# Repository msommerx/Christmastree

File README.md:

# Christmastree

Advent calendar in the shape of a Christmastree.  
Based on WS2812 LEDs and an ESP8266 combined with an DS3231 RTC for non WiFi environment.  

## Hardware
I used an WEMOS D1 Mini to controll the LEDs. If you have a WiFi in range, you don't need the DS3231. Just setup the WiFi on the ESP8266 and get your time via NTP.  
In my case there was no WiFi, so I needed an extra RTC.  
The WS2812 LEDs are connected in parallel. Everything can easyly be driven by a 5V DC Powersupply. 

## Software
Based on the WS2812FX Library, beginning at the 1st of a month, the first LED turns on. The 2nd the second LED turns on and so on.  
At the 24th of a month all LEDs are turned on until the 1st of the next month.  
To hold the time, even if the circuit was disconnected, I used a battery buffered DS3231.

## Circuit Layout
The Eagle layout has only less through-plating so it can easiely be made by your own. Also the wires are sized bigger including clearence between wires and pads.

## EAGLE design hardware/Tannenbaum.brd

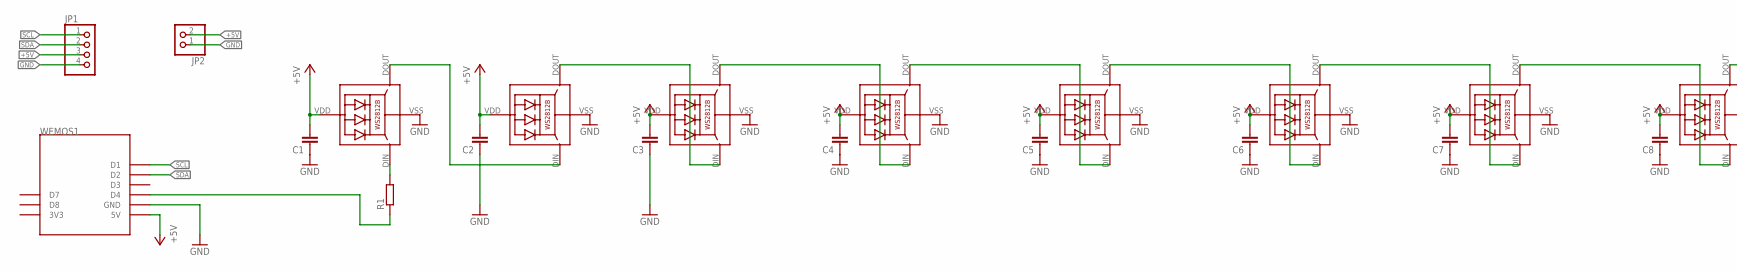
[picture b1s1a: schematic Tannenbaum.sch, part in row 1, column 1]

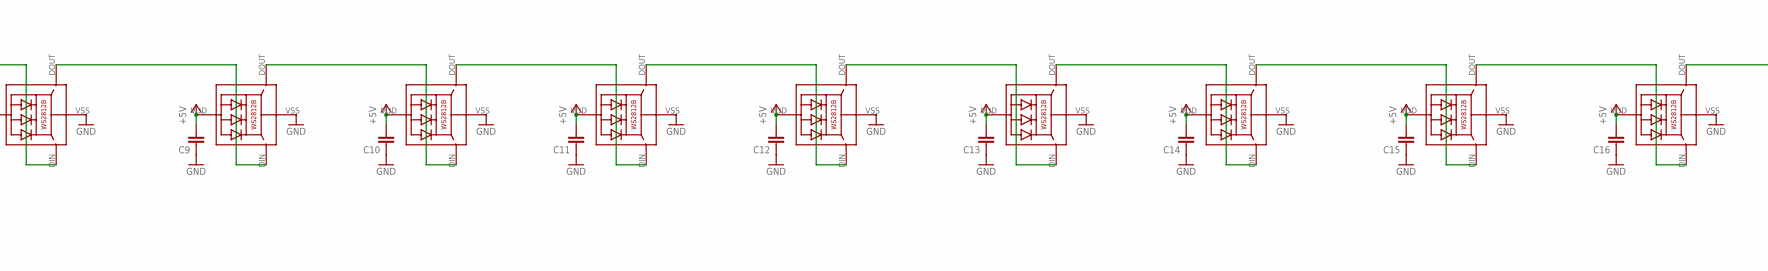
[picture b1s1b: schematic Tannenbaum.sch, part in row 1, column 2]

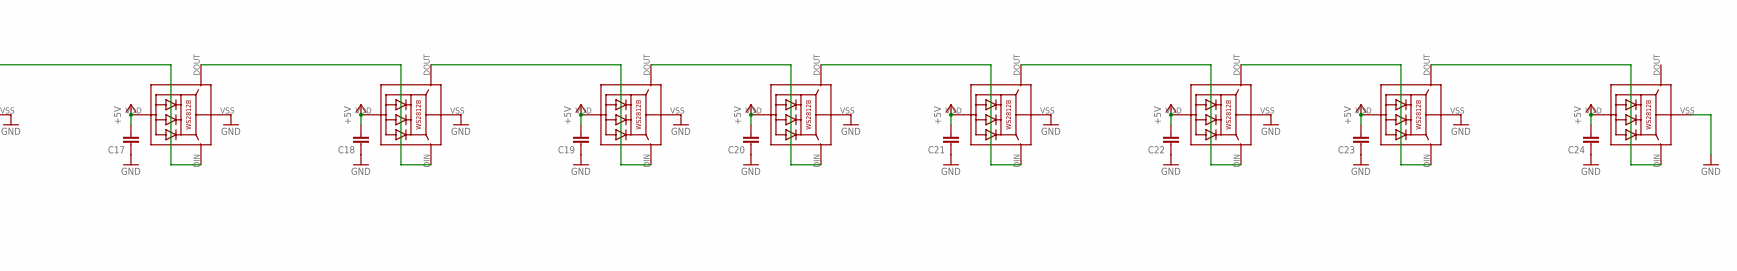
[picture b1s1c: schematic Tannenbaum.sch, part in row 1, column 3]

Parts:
C1, C2, C3, C4, C5, C6, C7, C8, C9, C10, C11, C12, C13, C14, C15, C16, C17, C18, C19, C20, C21, C22, C23, C24: C-EUC0805; C0805
JP1: PINHD-1X4; 1X04
JP2: PINHD-1X2; 1X02
LED1, LED2, LED3, LED4, LED5, LED6, LED7, LED8, LED9, LED10, LED11, LED12, LED13, LED14, LED15, LED16, LED17, LED18, LED19, LED20, LED21, LED22, LED23, LED24: WS2812B
R1: R-EU_R0805; R0805
WEMOS1: WEMOS-D1-MINI1

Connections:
+5V: C1.2, C2.2, C3.2, C4.2, C5.2, C6.2, C7.2, C8.2, C9.2, C10.2, C11.2, C12.2, C13.2, C14.2, C15.2, C16.2, C17.2, C18.2, C19.2, C20.2, C21.2, C22.2, C23.2, C24.2, JP1.3, JP2.2, LED1.VDD, LED2.VDD, LED3.VDD, LED4.VDD, LED5.VDD, LED6.VDD, LED7.VDD, LED8.VDD, LED9.VDD, LED10.VDD, LED11.VDD, LED12.VDD, LED13.VDD, LED14.VDD, LED15.VDD, LED16.VDD, LED17.VDD, LED18.VDD, LED19.VDD, LED20.VDD, LED21.VDD, LED22.VDD, LED23.VDD, LED24.VDD, WEMOS1.5V
GND: C1.1, C2.1, C3.1, C4.1, C5.1, C6.1, C7.1, C8.1, C9.1, C10.1, C11.1, C12.1, C13.1, C14.1, C15.1, C16.1, C17.1, C18.1, C19.1, C20.1, C21.1, C22.1, C23.1, C24.1, JP1.4, JP2.1, LED1.VSS (GND), LED2.VSS (GND), LED3.VSS (GND), LED4.VSS (GND), LED5.VSS (GND), LED6.VSS (GND), LED7.VSS (GND), LED8.VSS (GND), LED9.VSS (GND), LED10.VSS (GND), LED11.VSS (GND), LED12.VSS (GND), LED13.VSS (GND), LED14.VSS (GND), LED15.VSS (GND), LED16.VSS (GND), LED17.VSS (GND), LED18.VSS (GND), LED19.VSS (GND), LED20.VSS (GND), LED21.VSS (GND), LED22.VSS (GND), LED23.VSS (GND), LED24.VSS (GND), WEMOS1.GND
unnamed: LED1.DIN (DI), R1.2
unnamed: R1.1, WEMOS1.D4
unnamed: LED1.DOUT (DO), LED2.DIN (DI)
unnamed: LED2.DOUT (DO), LED3.DIN (DI)
unnamed: LED3.DOUT (DO), LED4.DIN (DI)
unnamed: LED4.DOUT (DO), LED5.DIN (DI)
unnamed: LED5.DOUT (DO), LED6.DIN (DI)
unnamed: LED6.DOUT (DO), LED7.DIN (DI)
unnamed: LED7.DOUT (DO), LED8.DIN (DI)
unnamed: LED8.DOUT (DO), LED9.DIN (DI)
unnamed: LED9.DOUT (DO), LED10.DIN (DI)
unnamed: LED10.DOUT (DO), LED11.DIN (DI)
unnamed: LED11.DOUT (DO), LED12.DIN (DI)
unnamed: LED12.DOUT (DO), LED13.DIN (DI)
unnamed: LED13.DOUT (DO), LED14.DIN (DI)
unnamed: LED14.DOUT (DO), LED15.DIN (DI)
unnamed: LED15.DOUT (DO), LED16.DIN (DI)
unnamed: LED16.DOUT (DO), LED17.DIN (DI)
unnamed: LED17.DOUT (DO), LED18.DIN (DI)
unnamed: LED18.DOUT (DO), LED19.DIN (DI)
unnamed: LED19.DOUT (DO), LED20.DIN (DI)
unnamed: LED20.DOUT (DO), LED21.DIN (DI)
unnamed: LED21.DOUT (DO), LED22.DIN (DI)
unnamed: LED22.DOUT (DO), LED23.DIN (DI)
unnamed: LED23.DOUT (DO), LED24.DIN (DI)
SCL: JP1.1, WEMOS1.D1
SDA: JP1.2, WEMOS1.D2

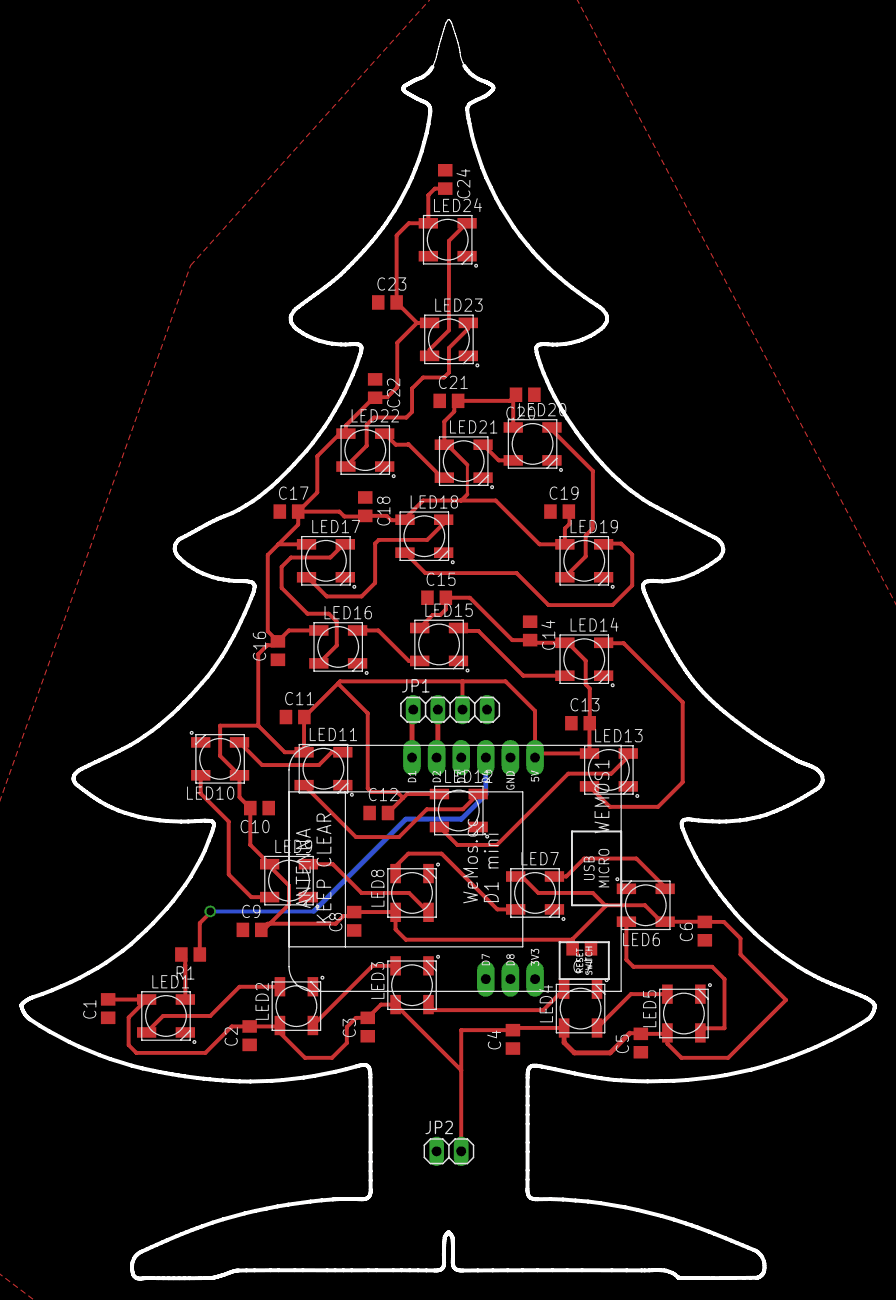
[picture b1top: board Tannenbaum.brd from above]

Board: 2 copper layers, 88.1 x 130.0 mm, 52 parts (0 on the bottom side), 29 nets.

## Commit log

2019-02-03 updated folderstructure
